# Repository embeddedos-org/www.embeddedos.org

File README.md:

# www.embeddedos.org

The public website of the Embedded Operating Systems Research Foundation.

Community resources: [Wiki](https://github.com/embeddedos-org/www.embeddedos.org/wiki) · [Discussions](https://github.com/orgs/embeddedos-org/discussions) · [Issues](https://github.com/embeddedos-org/www.embeddedos.org/issues) · [Projects](https://github.com/orgs/embeddedos-org/projects) · [AGENTS.md](https://github.com/embeddedos-org/www.embeddedos.org/blob/master/AGENTS.md)

A React single-page application that is **prerendered to static HTML at build
time** — every route ships as a real document with its own `<title>`, meta
description and canonical URL, readable without JavaScript.

**Production has no server process.** The site deploys to cPanel as the static
contents of `dist/public`, served by Apache. There is no `/api/trpc` in
production, and anything that assumes one is broken there even when it works
locally — that is how the careers form silently lost every application it
received, and why eBot and site search now answer entirely in the browser from
`shared/ebot-knowledge.ts` and `shared/site-index.ts`.

The Express + tRPC server in `server/` runs the **development** server and
backs the test suite. Treat any new tRPC procedure as dev-and-test-only unless
the hosting model changes.

---

## Requirements

| Tool    | Version used here | Notes                                                    |
| ------- | ----------------- | -------------------------------------------------------- |
| Node.js | 22                | Matches `.nvmrc`, `engines.node` and the version CI runs |
| pnpm    | 10.4.1            | Pinned by `packageManager` in `package.json`             |

`.nvmrc` pins the major version, so with nvm installed:

```bash
nvm use
```

On a machine where Node is installed in a local toolchain directory rather
than through a version manager, put it on `PATH` in every new shell instead:

```bash
export PATH="$HOME/.local/node/bin:$PATH"
```

Every command below assumes one of those has been done. If
`pnpm: command not found` is the first thing you see, this is why. Do not run
the `pnpm` shim that ships with corepack unless it has already downloaded
pnpm — it fetches on first use and will hang on a slow connection.

---

## Quick start

```bash
export PATH="$HOME/.local/node/bin:$PATH"
pnpm install
pnpm dev          # http://localhost:3000 (falls back to the next free port)
```

To run what actually ships — prerendered HTML, real 404s, the storage proxy —
build first and serve the production bundle:

```bash
pnpm build
pnpm start
```

`pnpm build` runs four steps in order, and all four matter:

1. `optimize:images` — re-encodes images in `client/public` (WebP variants)
2. `build:client` — vite builds the SPA into `dist/public`
3. `prerender` — headless Chromium renders all 133 routes to `<route>/index.html`,
   then `sitemap:dist` writes the sitemap for that exact build
4. `build:server` — esbuild bundles the API server to `dist/index.js`

Running `pnpm build:client` alone produces a build with **no prerendered
pages**. Never deploy that; see [Deployment](#deployment).

---

## Layout

```
client/          React SPA
  src/pages/     One component per route (134 <Route> declarations in App.tsx,
                 133 of them static and therefore prerendered)
  src/components/  Shared UI; components/ui/ is shadcn/Radix primitives
  public/        Copied verbatim into dist/public — including .htaccess and .cpanel.yml
server/          Express + tRPC API
  _core/         Server bootstrap, auth, storage proxy, vite middleware
  routers.ts     tRPC route definitions
shared/          Types and data used by both sides
docs/wiki/       Reviewable, byte-identical mirrors of the repository wiki
scripts/         Build and maintenance tooling (prerender, audits, deploy)
e2e/             Playwright suites
tests/           Vitest suites (unit, integration, security, performance)
drizzle/         Database schema and migrations
dist/            Build output — gitignored, and the source of the deploy branch
```

Governance documents (`CLAUDE.md`, `VERIFY.md`, `TESTING.md`, `SECURITY-STANDARDS.md`,
`AGENTS.md`, …) define how work on this repository is carried out and verified.
`CLAUDE.md` is the entry point and routes to the rest.

---

## Commands

### Build and run

| Command                             | Does                                                    |
| ----------------------------------- | ------------------------------------------------------- |
| `pnpm dev`                          | Development server with HMR                             |
| `pnpm build`                        | Full production build: client → prerender → server      |
| `pnpm build:client`                 | Client only — **no prerendering**, not deployable alone |
| `pnpm prerender`                    | Re-run prerendering against an existing `dist/public`   |
| `pnpm start`                        | Serve the production build                              |
| `pnpm check`                        | TypeScript, no emit                                     |
| `pnpm lint` / `pnpm lint:fix`       | ESLint                                                  |
| `pnpm format` / `pnpm format:check` | Prettier                                                |

### Tests

| Command                 | Covers                                                       |
| ----------------------- | ------------------------------------------------------------ |
| `pnpm test`             | All vitest suites (unit, integration, security, performance) |
| `pnpm test:unit`        | `tests/unit`                                                 |
| `pnpm test:integration` | `tests/integration`                                          |
| `pnpm test:security`    | `tests/security`                                             |
| `pnpm test:perf`        | `tests/performance` — payload budgets                        |
| `pnpm test:e2e`         | Every Playwright suite                                       |
| `pnpm test:smoke`       | `e2e/smoke.spec.ts`                                          |
| `pnpm test:regression`  | `e2e/regression.spec.ts` — one guard per fixed defect        |
| `pnpm test:a11y`        | `e2e/ui-ux.spec.ts` — axe accessibility checks               |
| `pnpm test:journeys`    | Navigation journeys, link and control sweeps                 |
| `pnpm test:controls`    | Clicks every in-page control on every route                  |
| `pnpm test:links`       | On-demand: clicks every internal link, checks where it lands |
| `pnpm test:functional`  | `e2e/functional.spec.ts`                                     |
| `pnpm test:acceptance`  | Google Ad Grants policy criteria                             |
| `pnpm test:server`      | `server/**` tRPC router tests                                |
| `pnpm test:all`         | check → lint → build → test → audits → e2e                   |

Three suites cover controls, and the differences matter — each catches what the
one before it cannot:

- `test:journeys` reads the **built HTML** and proves each of the ~9,000
  anchors resolves and each of the ~1,100 buttons carries an accessible name.
  It presses nothing.
- `test:controls` **clicks** every one of the ~340 in-page controls across all
  133 routes, plus the header and footer controls on a sample, and fails on any
  uncaught exception or console error. A control can pass the first suite and
  still throw on click.
- `test:links` clicks each of the ~320 unique internal links **from the bottom
  of its page** and asserts two things the others never check: that it lands on
  the route its href names, and that the page opens at the top.

`test:links` is **opt-in and skipped by `pnpm test:e2e`**, which is why it
needs its own command. It performs ~320 real navigations and proved sensitive
to machine load in a way the rest of the suite is not: under parallel workers a
different page each run reported resting a few hundred pixels down, and none of
it reproduced — twelve controlled navigations from the worst offender measured
y=0 every time, and none of the implicated pages contains scrolling, focus or
iframe code that could explain it. A check that fails one test in eighty for
reasons outside the code teaches people to ignore red, so it is a diagnostic
rather than a gate. The defects it originally found are guarded deterministically
by the scroll tests in `regression.spec.ts`, which fail when the fix is removed.

Run it before a release, and read a failure as "look at this", not "this is broken".

The Playwright suites run against the **production build**, and
`playwright.config.ts` starts `dist/index.js` for them. Run `pnpm build` first,
or the suite tests a stale build. Several tests read `dist/public` directly.

### Audits

| Command                | Does                                          |
| ---------------------- | --------------------------------------------- |
| `pnpm audit:site`      | Crawls the built site for structural problems |
| `pnpm audit:mobile`    | Mobile-viewport audit                         |
| `pnpm optimize:images` | Re-encodes images in `client/public`          |
| `pnpm sync:stack`      | Refreshes generated stack data                |

---

## Deployment

The site is hosted on **cPanel**, served by Apache as static files, and updated
through cPanel's Git Version Control feature.

### How the `deploy` branch works

`deploy` is an **orphan branch** — it shares no history with `master` — whose
root is exactly the contents of `dist/public`. It holds build output, not
source. Its commits read `deploy: rebuild from master <sha>`, which is the only
link back to the source they were built from.

```
master   ──●──●──●──●   source
                  │
                  │  pnpm build  →  dist/public
                  ▼
deploy   ──●──●──●       built site, root = dist/public
                  │
                  ▼  cPanel: Update from Remote → Deploy HEAD Commit
             public_html/
```

Two files make this work, and both live in `client/public/` so that **vite
copies them into every build**:

- **`.htaccess`** — `Options -Indexes` and `ErrorDocument 404 /404.html`.
  Deliberately **no SPA rewrite**: the prerenderer writes every route to
  `<route>/index.html`, so Apache's ordinary file resolution already serves
  them. A blanket rewrite to `/index.html` answers unknown URLs with HTTP 200
  and the homepage — a soft 404 that search engines index as a real page.
- **`.cpanel.yml`** — the tasks cPanel runs on deploy. It copies `*` plus
  `.htaccess` by name, because the `*` glob skips dotfiles. There is no delete
  step: overwriting is safe, emptying a directory is not. Before copying the
  build, it appends `session.upload_progress.enabled = 0` to
  `public_html/.user.ini` unless the file already ends up at 0, a stopgap for
  #128 that `.htaccess` repeats for module handlers; `.htaccess` also denies
  web access to `.user.ini`. It appends rather than copies so the host's own
  PHP settings in that file survive. The fix for #128 is still upgrading the
  host's PHP in cPanel.
  Each deploy replaces `public_html/.htaccess`. Under some PHP handlers
  cPanel's MultiPHP Manager and INI Editor write their settings into that
  file, so check the live file before changing PHP in cPanel, or the next
  deploy will drop those settings.

They live in `client/public/` rather than being committed to `deploy` directly
because that was tried and it failed — a file added to the deploy branch by hand
is deleted by the next rebuild, which is exactly how `.htaccess` once went
missing from production. `tests/integration/deploy-config.test.ts` asserts both
files reach `dist/public` and that the rules inside them are still correct.

### Deploying

The one-command path — build, publish to the `deploy` branch, push:

```bash
./deploy.sh                     # full pipeline, pushes to origin
./deploy.sh --no-push           # stop after committing to deploy, for review
```

Or the manual steps, which `./deploy.sh` chains for you:

```bash
export PATH="$HOME/.local/node/bin:$PATH"

# 1. Everything must be green and committed first.
pnpm test:all
git status --porcelain          # must be empty

# 2. Build, then publish the build to the deploy branch.
pnpm build
pnpm deploy:branch              # commits to deploy, does NOT push
git log deploy -1 --stat        # review what is about to ship
pnpm deploy:branch --push       # or: git push origin deploy
```

`scripts/deploy-branch.mjs` does the mechanical part through a throwaway git
worktree, so the checkout you are working in is never switched to `deploy`
mid-run. It refuses to proceed if:

- there is no build in `dist/public`;
- fewer than 50 routes were prerendered (i.e. `build:client` was run without
  `prerender`);
- `.htaccess` or `.cpanel.yml` is missing from the build;
- the working tree is dirty, which would make the recorded source sha a lie.

It replaces the branch contents wholesale, so superseded content-hashed bundles
are pruned from the branch rather than accumulating.

**Pushing is not deploying.** cPanel does not act on a push. Finish in the
cPanel UI:

> Git Version Control → Manage (for this repository) → **Update from Remote**,
> then **Deploy HEAD Commit**.

`DEPLOYPATH` in `.cpanel.yml` is `$HOME/public_html`. Change it if this domain's
document root is elsewhere — an addon domain or subdomain has its own directory.

### Rolling back

The deploy branch is an ordinary branch, so a rollback is a revert plus another
deploy:

```bash
git checkout deploy
git revert --no-edit HEAD        # or: git reset --hard <known-good-sha>
git push origin deploy           # --force-with-lease if you reset
# then in cPanel: Update from Remote → Deploy HEAD Commit
```

Because `.cpanel.yml` has no delete step, files removed in a later build are
**not** removed from the document root by deploying an earlier commit. Files
that must genuinely disappear from production have to be deleted on the server.

---

## Environment variables

There is no `.env.example` in the repository. The following are the variables
referenced in the source; the site builds and serves its static content without
them, but the API features that use them are inert when unset.

| Variable                                           | Used for                                                                                                                                                                                            |
| -------------------------------------------------- | --------------------------------------------------------------------------------------------------------------------------------------------------------------------------------------------------- |
| `PORT`                                             | Server port (default 3000; the server scans forward for a free one)                                                                                                                                 |
| `NODE_ENV`                                         | `development` / `production`                                                                                                                                                                        |
| `DATABASE_URL`                                     | MySQL connection for drizzle                                                                                                                                                                        |
| `JWT_SECRET`                                       | Cookie/session signing                                                                                                                                                                              |
| `OAUTH_SERVER_URL`, `OWNER_OPEN_ID`, `VITE_APP_ID` | OAuth integration                                                                                                                                                                                   |
| `STRIPE_SECRET_KEY`                                | Card payments on /donate (Stripe secret key — set on the host only, never in git; see `docs/STRIPE-SECRET-KEY.md`)                                                                                  |
| `SMTP_HOST`, `SMTP_PORT`, `SMTP_USER`, `SMTP_PASS` | Outbound email                                                                                                                                                                                      |
| `BUILT_IN_FORGE_API_URL`, `BUILT_IN_FORGE_API_KEY` | Manus Forge API — backs the dev/test-only owner-notification and image-storage-proxy code paths in `server/_core/`. Not used in production; the live careers form posts to `/api/apply.php` instead |
| `SITE_ORIGIN`                                      | Canonical origin used by the prerenderer (default `https://www.embeddedos.org`)                                                                                                                     |
| `PRERENDER_PORT`, `PRERENDER_CONCURRENCY`          | Prerender tuning                                                                                                                                                                                    |
| `E2E_PORT`                                         | Port Playwright's server uses (default 42200)                                                                                                                                                       |

Database schema changes go through `pnpm db:push` (drizzle-kit generate +
migrate).

---

## Booking

`/book` is the booking page, linked as "Book a call" in the header. `/contact`
and `/eos-boards` each carry a compact card that links to it. The page is
`client/src/pages/Book.tsx`: it lists the topics as guidance and embeds the
Foundation's Google Calendar appointment schedule
(`client/src/components/BookingCalendar.tsx`), where the visitor picks a time
and fills in Google's booking form. Topics, durations, the "what to expect"
list and the FAQ are in `client/src/data/booking.ts`.

- **The calendar is two constants** in `client/src/data/foundation.ts`:
  - `GOOGLE_APPOINTMENTS_EMBED_URL`, the iframe `src` from the schedule's
    embed code, now
    `https://calendar.google.com/calendar/appointments/AcZssZ3QwWoaBjMsLfr11qrGiRxBA4URKeZ8Zu-5bv0=?gv=true`;
  - `GOOGLE_BOOKING_PAGE_URL`, the schedule's booking page link, now
    `https://calendar.app.google/PPzWao4AzvXtZeva6`. It sits under the
    calendar as "Open the booking page" and opens in a new tab.
- **To change the calendar,** open the appointment schedule in Google
  Calendar and use its share options: copy the booking page link into
  `GOOGLE_BOOKING_PAGE_URL`, and from the website embed code copy only the
  `src` of the `<iframe>` into `GOOGLE_APPOINTMENTS_EMBED_URL`. Do not paste
  Google's "Book an appointment" button code: it loads
  `scheduling-button-script.js` and a stylesheet from Google, which the CSP
  does not allow and the site does not use. `client/src/lib/booking.ts`
  accepts only these forms:
  - embed: `https://calendar.google.com/calendar/appointments/<id>?gv=true`
    (optionally `appointments/schedules/<id>`);
  - booking page: `https://calendar.app.google/<id>`, or the
    `https://calendar.google.com/calendar/appointments/...` address without
    the query.

  Then update `tests/unit/booking-url-set.test.tsx`, which pins both values.
  An embed URL that does not pass the check shows the email fallback instead
  of a calendar, with the `_BY_EMAIL` versions of the steps, the "what to
  expect" list, the time-zone note and the FAQ, which promise only an email
  reply; a booking link that does not pass is left out.

- **Set in Google Calendar, not here:** the slot length, the video link and the
  booking form. The cards and copy say 30 minutes (`BOOKING_MINUTES`) and a
  video link in the confirmation email, so the schedule must use 30-minute
  slots with Google Meet (or another video link). The page asks visitors to
  mention their topic in the booking form, which by default asks only for a
  first name, a last name and an email address, so give the form an item such
  as "What would you like to talk about?". Nothing in this repository can check these settings;
  confirm them on the schedule.
- **The topic can no longer be passed in:** Google's embed takes no prefill,
  so the topic cards are guidance, not inputs, and the three steps are a guide
  rather than a progress bar.
- **Loading:** the iframe is mounted when the card comes within 300 px of the
  viewport, never while the site is prerendered, and carries
  `loading="lazy"`. A skeleton shows until the frame's load event. If that has
  not fired after 15 s (`FRAME_TIMEOUT_MS`), the card offers the booking page
  and the email option over it, and the calendar takes over again if it loads
  after all. The browser fires load even for an error page in the frame, so
  the link under the calendar is always shown.
- **CSP:** `client/public/.htaccess` allows `https://calendar.google.com` in
  `frame-src` and adds no Google script or style host for the calendar.
- **Notifications:** the embedded calendar tells this site nothing about a
  booking, so the site sends no notice of its own and stores nothing. Google
  adds each booking to the schedule owner's calendar ("When someone books an
  appointment, it's added to your calendar", Google Calendar Help). Any email
  about it, to the booker or to the team, is decided by the appointment
  schedule's own settings in Google Calendar, which also set up "confirmation
  emails and reminders" (Google Calendar Help, "Create an appointment
  schedule"). Check there that the booker gets a confirmation email, which the
  FAQ promises along with its cancel link, and that the team learns of each
  booking, by email or by watching the calendar.
- **`client/public/api/booking.php` is retired.** It used to mail the team a
  notice posted by the previous calendar. It now answers every request with
  HTTP 410 and does nothing else (`tests/php/booking-retired.test.php` and
  `tests/unit/booking.test.tsx` pin that). It stays because the cPanel deploy
  (`client/public/.cpanel.yml`) copies files and never deletes: removed from
  the repository, the old endpoint would stay live on the server. After this
  version is deployed, delete `public_html/api/booking.php` on the server, then
  delete the file here. That deletion turns CI's `deploy-drift` job red until
  the deploy branch is next rebuilt with `scripts/deploy-branch.mjs`, because
  `scripts/check-deploy-drift.mjs` fails on files the deploy branch has and the
  build does not; rebuild it soon after.

## Notes for contributors

- **Do not render `<Navbar />` or `<Footer />` inside a page.** `App.tsx`
  renders both around `<main>` for the whole application. A page that adds its
  own produces a second `position: fixed; z-50` header which, being later in the
  DOM, silently swallows every click aimed at the real one. This shipped once
  and disabled the navigation on all 13 product pages and `/patents`.
  `e2e/links-and-controls.spec.ts` now fails the build if it recurs.
- **Every route needs a prerendered page.** Routes are discovered from the
  literal `<Route path="...">` strings in `App.tsx`; anything dynamic is skipped
  and will 404 on the static host. `tests/integration/deploy-config.test.ts`
  checks each discovered route has a file.
- **Never hand-write a stack figure.** Board counts, platform counts, repo
  counts and architecture counts come from `shared/stack-data.ts` via
  `client/src/data/stack.ts` — import the constant, do not type the number.
  Hand-written figures have drifted twice: "52+" survived on seventeen pages,
  and after that purge "63+" survived on nineteen more, describing EoSim's
  150 simulated _platforms_ as 63 _boards_ and colliding with the kernel's 83
  board definitions. `tests/integration/stack-claims.test.ts` scans every built
  page and fails if a retired figure reappears. `/news` is exempt: its posts
  are dated announcements, and rewriting one revises the record rather than
  correcting a claim.
- **`<head>` is stamped twice, by two implementations that must agree.**
  `scripts/prerender.mjs` writes it at build time; `client/src/lib/page-meta.ts`
  rewrites it after a client-side navigation, because wouter swaps the page
  without touching `<head>` and the canonical URL would otherwise keep naming
  the first page visited. The build script cannot be imported into the bundle
  (it pulls in playwright and express), so the logic is deliberately duplicated
  and `tests/unit/page-meta.test.ts` asserts the two agree.
- **A route change must reset the scroll position.** wouter swaps the page
  component and leaves the viewport alone, so a link followed from the footer
  opened the next page already scrolled down — the browser clamps the old
  offset to the new document's height. `ScrollToTop` in `App.tsx` handles it,
  and three cases are easy to get wrong: the jump must be `behavior: "instant"`
  because `index.css` sets `scroll-behavior: smooth` for in-page anchors; a
  link to the route **already open** produces no location change at all, so it
  needs a capture-phase click listener (wouter's `Link` calls `preventDefault`,
  which makes a bubble-phase listener useless); and a `#hash` target must win
  over the jump to the top.
- **Never call `scrollIntoView` to follow a list.** It scrolls _every_ ancestor
  scroll container, including the document. `/demo` auto-scrolled its simulator
  log that way and the effect ran on mount, so opening the page dropped the
  visitor below the heading. Set the container's own `scrollTop` instead.
- **A modal must take focus.** The donate dialog shipped with
  `aria-modal="true"` and focus left on `<body>`, so one Tab reached the
  navigation behind the overlay. If you add an overlay, move focus into it,
  trap Tab, restore focus on close, and close on Escape.
- **`flex-1` without `min-w-0` overflows on a phone.** A flex item defaults to
  `min-width: auto`, so a code block or long string inside sizes the item to its
  content and pushes the document wider than the viewport. Six pages shipped
  this way. Wide tables need their own `overflow-x-auto` wrapper for the same
  reason.
- **framer-motion cannot tween an SVG `d` attribute.** It emits
  `d="undefined"` mid-tween. Animate a transform instead. An entry animation
  that starts at `x: ±20` also overflows a 375px viewport until it settles —
  clip the section.
- Payload budgets are enforced in `tests/performance/budgets.test.ts`; adding a
  large eager import will fail the suite rather than quietly regress the site.
- **A new board on `/eos-boards` is one manifest entry plus its media, its
  two KiCad files and its licence.** Add the board to `EOS_BOARDS` in
  `client/src/data/eos-boards.ts`, copying its facts from the board's
  `README.md` and its check counts from `build-report.json` and `drc.json` in
  eCAD-Hardware-Products. Put its media in `client/public/media/`:
  `board-<slug>-iso.jpg`, `-top.jpg` and `-bottom.jpg` from the board's
  renders, `board-<slug>-thumb.jpg` (the iso render at 480 px, for the index),
  `board-<slug>-turntable.mp4` (H.264, no audio) and
  `board-<slug>-turntable-poster.jpg` (the video's first frame). Copy, unchanged
  and from the commit in `checks.commit`, its native files
  `boards/eos/<slug>/hardware/<slug>.kicad_sch` and `<slug>.kicad_pcb` to
  `client/public/cad/<slug>/`, and its `boards/eos/<slug>/LICENSE.txt` to
  `client/public/board-licences/<slug>.txt` (`git show <commit>:<path>` in
  eCAD-Hardware-Products gives the exact bytes).
  Set `source` to `BOARD_SOURCES.merged`: the page lists only boards merged on
  eCAD-Hardware-Products master. Set `checks.commit` to the commit its counts
  come from. Then run `pnpm optimize:images` for the WebP siblings and the manifest.
  `tests/unit/eos-boards.test.tsx` fails if a media, KiCad or licence file is
  missing, a declared pixel size is wrong, or a KiCad file or licence does not
  carry the owner's name and terms.

---

## Licence

MIT, except the EmbeddedOS development-board renders and turntable videos in
`client/public/media/board-*`, the boards' native KiCad files in
`client/public/cad/`, and the board licences in `client/public/board-licences/`
(each board's `LICENSE.txt`, unchanged). Those are Copyright (c) 2026
Kartikeydheer Srivastava, all rights reserved, and are published here for
viewing under each board's `LICENSE.txt` in eCAD-Hardware-Products; see
`/eos-boards`. Third-party material in a board keeps its own licence, as that
board's licence lists.

See [SECURITY.md](./SECURITY.md) for the vulnerability disclosure policy.

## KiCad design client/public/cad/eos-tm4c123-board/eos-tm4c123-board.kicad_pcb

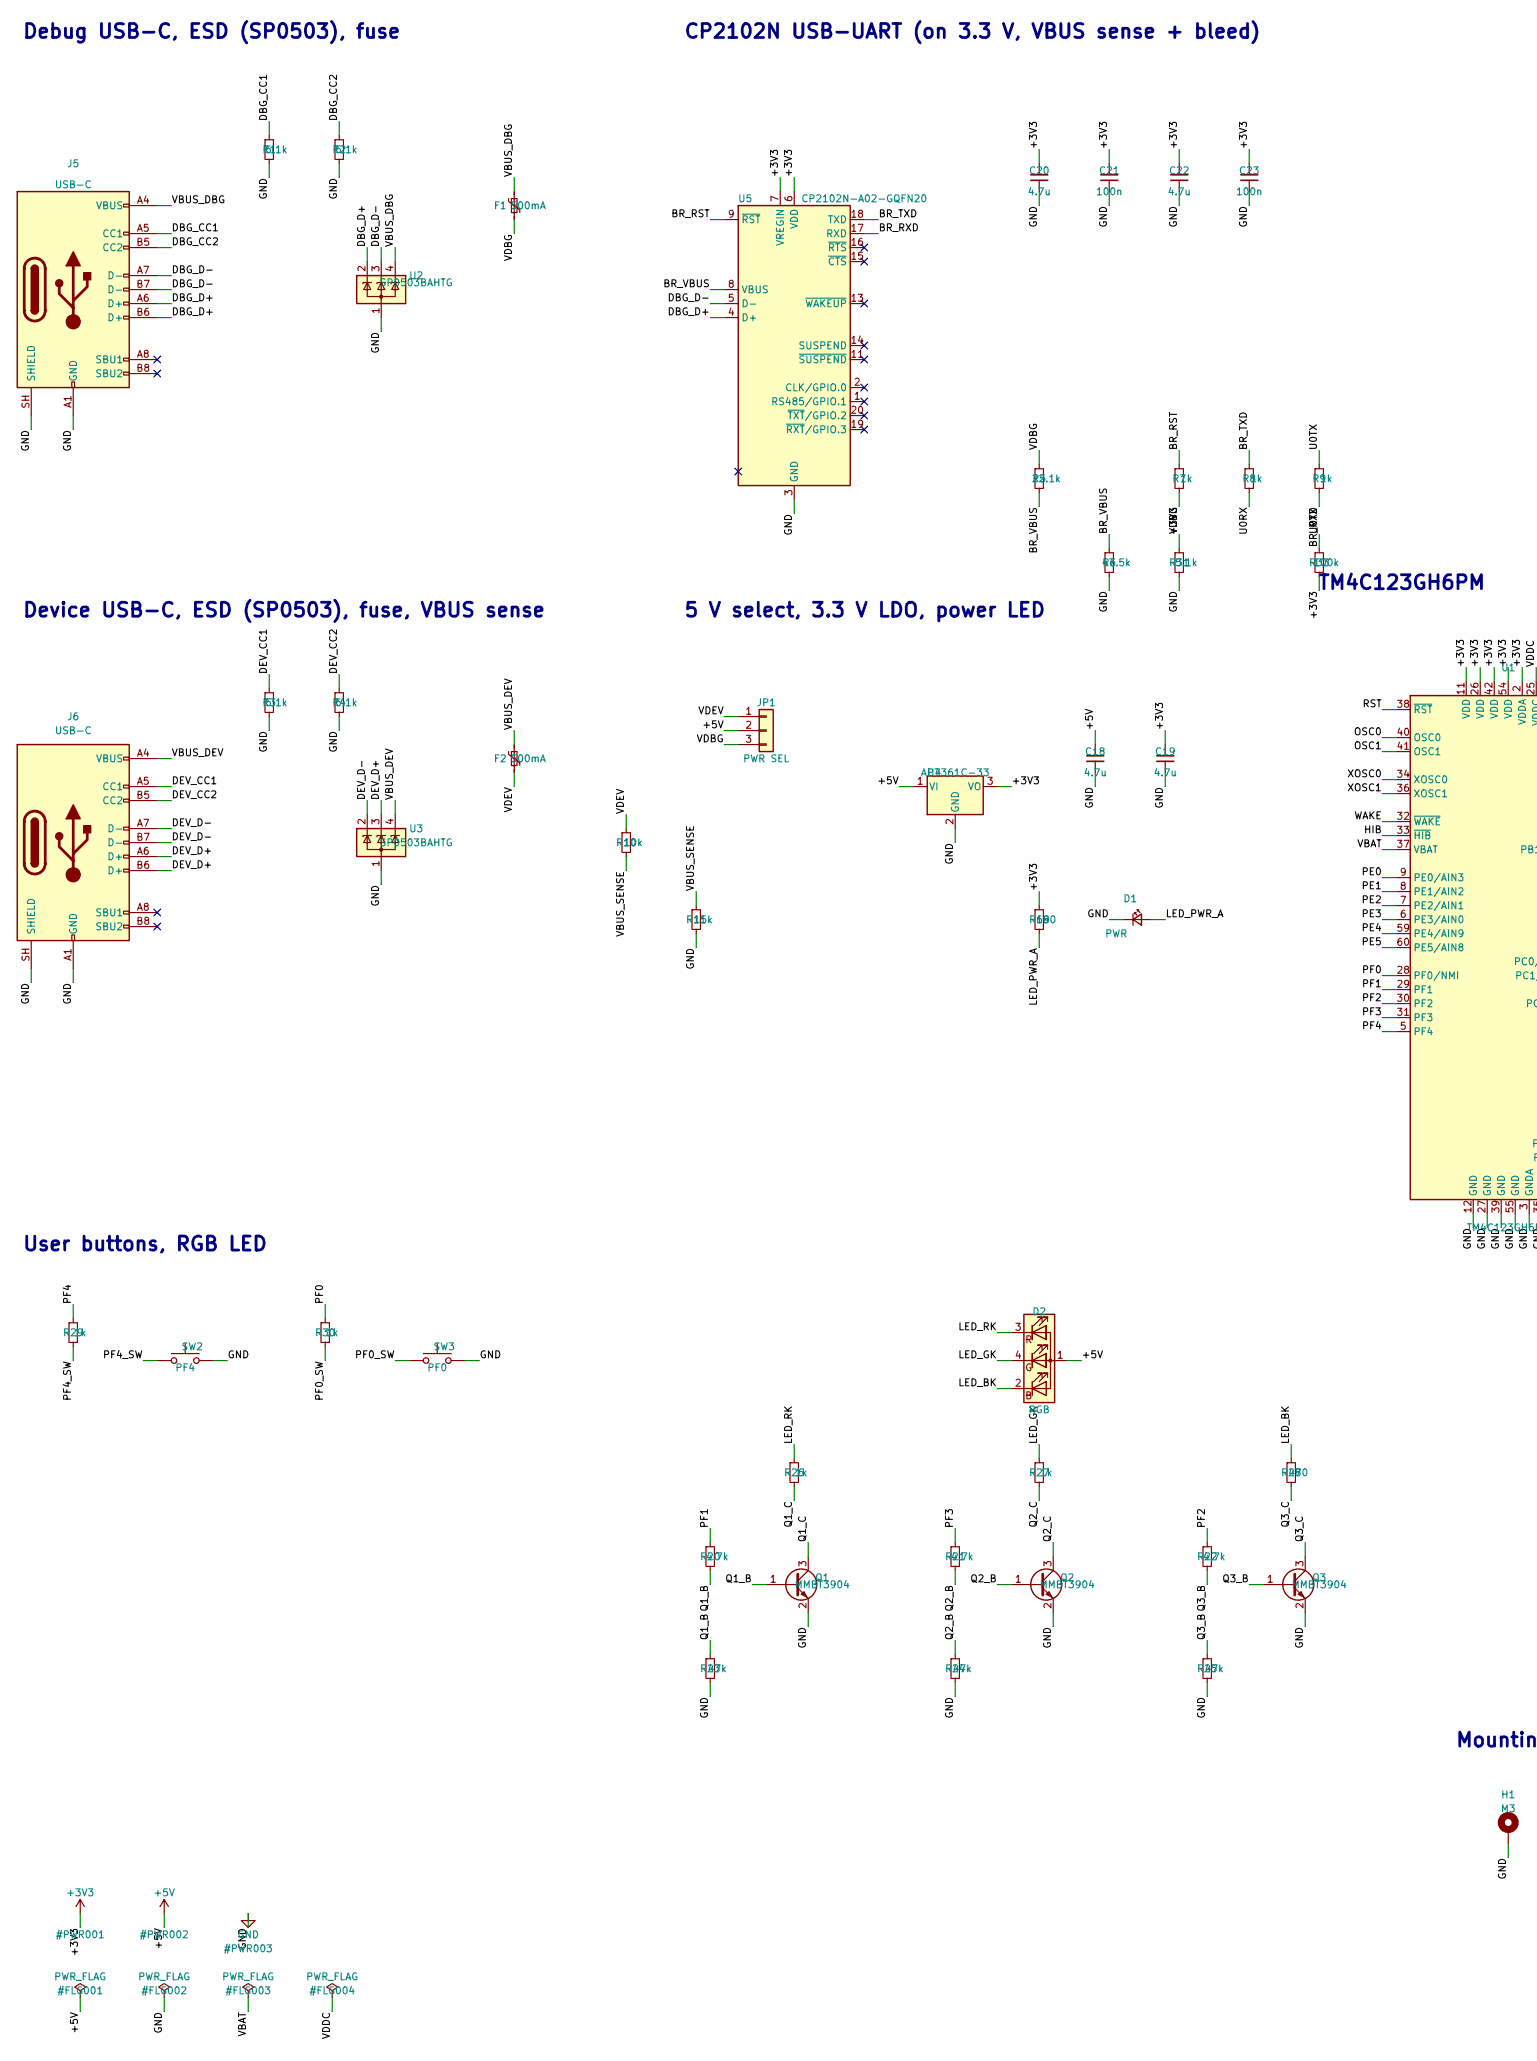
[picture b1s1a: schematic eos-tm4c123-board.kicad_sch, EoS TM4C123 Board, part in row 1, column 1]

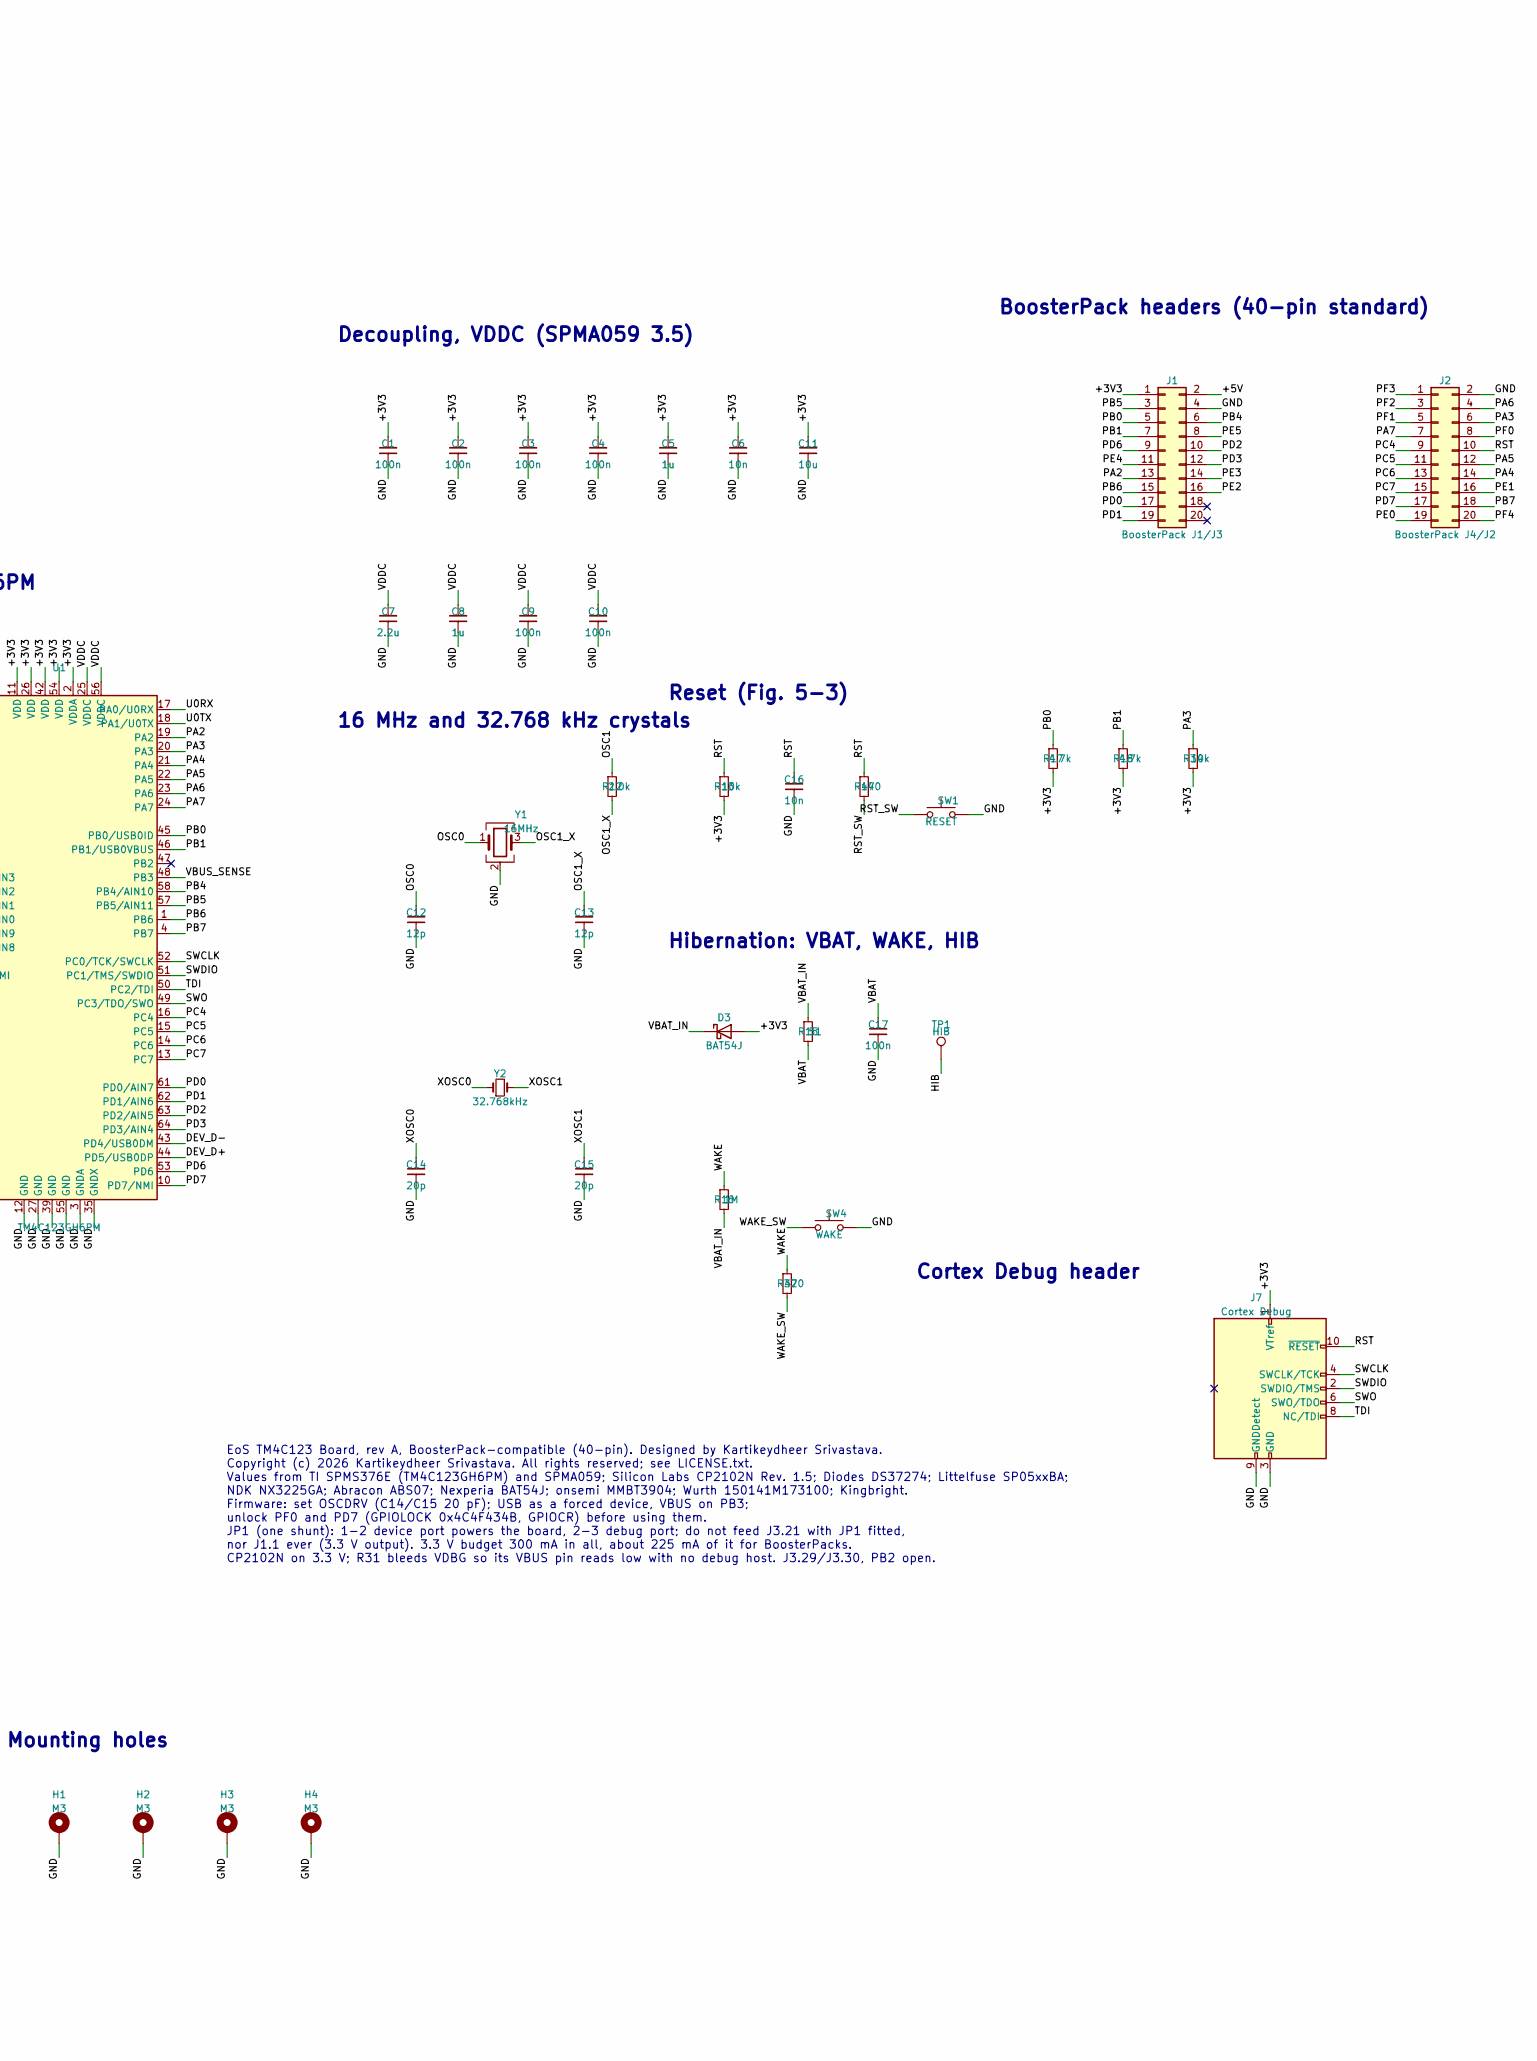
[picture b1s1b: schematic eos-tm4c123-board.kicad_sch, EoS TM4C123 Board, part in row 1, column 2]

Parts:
C1, C2, C3, C4, C9, C10, C17, C21, C23: 100n; C_0402_1005Metric; MPN GRM155R71C104KA88D
C5, C8: 1u; C_0603_1608Metric; MPN GRM188R71C105KA12D
C6, C16: 10n; C_0402_1005Metric; MPN GRM155R71H103KA88D
C7: 2.2u; C_0603_1608Metric; MPN GRM188R71A225KE15D
C11: 10u; C_0805_2012Metric; MPN GRM21BR61A106KE19L
C12, C13: 12p; C_0402_1005Metric; MPN GRM1555C1H120JA01D
C14, C15: 20p; C_0402_1005Metric; MPN GRM1555C1H200JA01D
C18, C19: 4.7u; C_0805_2012Metric; MPN GRM21BR61A475KA73L
C20, C22: 4.7u; C_0603_1608Metric; MPN GRM188R61A475KE15D
D1: PWR; LED_0603_1608Metric; MPN APTD1608LCGCK
D2: RGB; LED_RGB_Wuerth-PLCC4_3.2x2.8mm_150141M173100; MPN 150141M173100
D3: BAT54J; D_SOD-323F; MPN BAT54J
F1, F2: 500mA; Fuse_1206_3216Metric; MPN 1206L050YR
H1, H2, H3, H4: M3; MountingHole_3.2mm_M3_Pad_Via
J1: BoosterPack J1/J3; PinHeader_2x10_P2.54mm_Vertical; MPN SSW-110-23-F-D
J2: BoosterPack J4/J2; PinHeader_2x10_P2.54mm_Vertical; MPN SSW-110-23-F-D
J5, J6: USB-C; USB_C_Receptacle_HRO_TYPE-C-31-M-12; MPN TYPE-C-31-M-12
J7: Cortex Debug; PinHeader_2x05_P1.27mm_Vertical_SMD; MPN FTSH-105-01-L-DV-K
JP1: PWR SEL; PinHeader_1x03_P2.54mm_Vertical
Q1, Q2, Q3: MMBT3904; SOT-23; MPN MMBT3904LT1G
R1, R2, R3, R4, R31: 5.1k; R_0402_1005Metric
R5: 22.1k; R_0402_1005Metric
R6: 47.5k; R_0402_1005Metric
R7, R8, R9, R26, R27, R29, R30: 1k; R_0402_1005Metric
R10, R13, R34: 10k; R_0402_1005Metric
R11: 15k; R_0402_1005Metric
R12: 2.0k; R_0402_1005Metric
R14, R28, R32: 470; R_0402_1005Metric
R15: 51; R_0402_1005Metric
R16: 1M; R_0402_1005Metric
R17, R18, R20, R21, R22: 4.7k; R_0402_1005Metric
R19: 680; R_0402_1005Metric
R23, R24, R25: 47k; R_0402_1005Metric
R33: 100k; R_0402_1005Metric
SW1: RESET; SW_Push_1P1T_NO_CK_KMR2; MPN KMR221G LFS
SW2: PF4; SW_Push_1P1T_NO_CK_KMR2; MPN KMR221G LFS
SW3: PF0; SW_Push_1P1T_NO_CK_KMR2; MPN KMR221G LFS
SW4: WAKE; SW_Push_1P1T_NO_CK_KMR2; MPN KMR221G LFS
TP1: HIB; TestPoint_Pad_D1.0mm
U1: TM4C123GH6PM; LQFP-64_10x10mm_P0.5mm; MPN TM4C123GH6PMI
U2, U3: SP0503BAHTG; SOT-143; MPN SP0503BAHTG
U4: AP7361C-33; SOT-223-3_TabPin2; MPN AP7361C-33E-13
U5: CP2102N-A02-GQFN20; SiliconLabs_QFN-20-1EP_3x3mm_P0.5mm_EP1.8x1.8mm; MPN CP2102N-A02-GQFN20R
Y1: 16MHz; Crystal_SMD_3225-4Pin_3.2x2.5mm; MPN NX3225GA-16.000M-STD-CRG-2
Y2: 32.768kHz; Crystal_SMD_3215-2Pin_3.2x1.5mm; MPN ABS07-32.768KHZ-T

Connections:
+3V3: C1.1, C2.1, C3.1, C4.1, C5.1, C6.1, C11.1, C19.1, C20.1, C21.1, C22.1, C23.1, D3.2 (A), J1.1, J7.1 (VTref), R7.2, R13.2, R17.2, R18.2, R19.1, R33.2, R34.2, U1.2 (VDDA), U1.11 (VDD), U1.26 (VDD), U1.42 (VDD), U1.54 (VDD), U4.3 (VO), U5.6 (VDD), U5.7 (VREGIN)
+5V: C18.1, D2.1 (A), J1.2, JP1.2, U4.1 (VI)
/BR_RST: R7.1, U5.9 (~RST)
/BR_RXD: R9.2, U5.17 (RXD)
/BR_TXD: R8.1, U5.18 (TXD)
/BR_VBUS: R5.2, R6.1, U5.8 (VBUS)
/DBG_CC1: J5.A5 (CC1), R1.1
/DBG_CC2: J5.B5 (CC2), R2.1
/DBG_D+: J5.A6 (D+), J5.B6 (D+), U2.2 (K), U5.4 (D+)
/DBG_D-: J5.A7 (D-), J5.B7 (D-), U2.3 (K), U5.5 (D-)
/DEV_CC1: J6.A5 (CC1), R3.1
/DEV_CC2: J6.B5 (CC2), R4.1
/DEV_D+: J6.A6 (D+), J6.B6 (D+), U1.44 (PD5/USB0DP), U3.3 (K)
/DEV_D-: J6.A7 (D-), J6.B7 (D-), U1.43 (PD4/USB0DM), U3.2 (K)
/HIB: TP1.1, U1.33 (~HIB)
/LED_BK: D2.2 (BK), R28.1
/LED_GK: D2.4 (GK), R27.1
/LED_PWR_A: D1.2 (A), R19.2
/LED_RK: D2.3 (RK), R26.1
/OSC0: C12.1, U1.40 (OSC0), Y1.1
/OSC1: R12.1, U1.41 (OSC1)
/OSC1_X: C13.1, R12.2, Y1.3
/PA2: J1.13, U1.19 (PA2)
/PA3: J2.6, R34.1, U1.20 (PA3)
/PA4: J2.14, U1.21 (PA4)
/PA5: J2.12, U1.22 (PA5)
/PA6: J2.4, U1.23 (PA6)
/PA7: J2.7, U1.24 (PA7)
/PB0: J1.5, R17.1, U1.45 (PB0/USB0ID)
/PB1: J1.7, R18.1, U1.46 (PB1/USB0VBUS)
/PB4: J1.6, U1.58 (PB4/AIN10)
/PB5: J1.3, U1.57 (PB5/AIN11)
/PB6: J1.15, U1.1 (PB6)
/PB7: J2.18, U1.4 (PB7)
/PC4: J2.9, U1.16 (PC4)
/PC5: J2.11, U1.15 (PC5)
/PC6: J2.13, U1.14 (PC6)
/PC7: J2.15, U1.13 (PC7)
/PD0: J1.17, U1.61 (PD0/AIN7)
/PD1: J1.19, U1.62 (PD1/AIN6)
/PD2: J1.10, U1.63 (PD2/AIN5)
/PD3: J1.12, U1.64 (PD3/AIN4)
/PD6: J1.9, U1.53 (PD6)
/PD7: J2.17, U1.10 (PD7/NMI)
/PE0: J2.19, U1.9 (PE0/AIN3)
/PE1: J2.16, U1.8 (PE1/AIN2)
/PE2: J1.16, U1.7 (PE2/AIN1)
/PE3: J1.14, U1.6 (PE3/AIN0)
/PE4: J1.11, U1.59 (PE4/AIN9)
/PE5: J1.8, U1.60 (PE5/AIN8)
/PF0: J2.8, R30.1, U1.28 (PF0/NMI)
/PF0_SW: R30.2, SW3.1
/PF1: J2.5, R20.1, U1.29 (PF1)
/PF2: J2.3, R22.1, U1.30 (PF2)
/PF3: J2.1, R21.1, U1.31 (PF3)
/PF4: J2.20, R29.1, U1.5 (PF4)
/PF4_SW: R29.2, SW2.1
/Q1_B: Q1.1 (B), R20.2, R23.1
/Q1_C: Q1.3 (C), R26.2
/Q2_B: Q2.1 (B), R21.2, R24.1
/Q2_C: Q2.3 (C), R27.2
/Q3_B: Q3.1 (B), R22.2, R25.1
/Q3_C: Q3.3 (C), R28.2
/RST: C16.1, J2.10, J7.10 (~RESET), R13.1, R14.1, U1.38 (~RST)
/RST_SW: R14.2, SW1.1
/SWCLK: J7.4 (SWCLK/TCK), U1.52 (PC0/TCK/SWCLK)
/SWDIO: J7.2 (SWDIO/TMS), U1.51 (PC1/TMS/SWDIO)
/SWO: J7.6 (SWO/TDO), U1.49 (PC3/TDO/SWO)
/TDI: J7.8 (NC/TDI), U1.50 (PC2/TDI)
/U0RX: R8.2, U1.17 (PA0/U0RX)
/U0TX: R9.1, R33.1, U1.18 (PA1/U0TX)
/VBAT: C17.1, R15.2, U1.37 (VBAT)
/VBAT_IN: D3.1 (K), R15.1, R16.2
/VBUS_DBG: F1.1, J5.A4 (VBUS), J5.A9 (VBUS), J5.B4 (VBUS), J5.B9 (VBUS), U2.4 (K)
/VBUS_DEV: F2.1, J6.A4 (VBUS), J6.A9 (VBUS), J6.B4 (VBUS), J6.B9 (VBUS), U3.4 (K)
/VBUS_SENSE: R10.2, R11.1, U1.48 (PB3)
/VDBG: F1.2, JP1.3, R5.1, R31.1
/VDDC: C7.1, C8.1, C9.1, C10.1, U1.25 (VDDC), U1.56 (VDDC)
/VDEV: F2.2, JP1.1, R10.1
/WAKE: R16.1, R32.1, U1.32 (~WAKE)
/WAKE_SW: R32.2, SW4.1
/XOSC0: C14.1, U1.34 (XOSC0), Y2.1
/XOSC1: C15.1, U1.36 (XOSC1), Y2.2
GND: C1.2, C2.2, C3.2, C4.2, C5.2, C6.2, C7.2, C8.2, C9.2, C10.2, C11.2, C12.2, C13.2, C14.2, C15.2, C16.2, C17.2, C18.2, C19.2, C20.2, C21.2, C22.2, C23.2, D1.1 (K), H1.1, H2.1, H3.1, H4.1, J1.4, J2.2, J5.A1 (GND), J5.A12 (GND), J5.B1 (GND), J5.B12 (GND), J5.SH (SHIELD), J6.A1 (GND), J6.A12 (GND), J6.B1 (GND), J6.B12 (GND), J6.SH (SHIELD), J7.3 (GND), J7.5 (GND), J7.9 (GNDDetect), Q1.2 (E), Q2.2 (E), Q3.2 (E), R1.2, R2.2, R3.2, R4.2, R6.2, R11.2, R23.2, R24.2, R25.2, R31.2, SW1.2, SW2.2, SW3.2, SW4.2, U1.3 (GNDA), U1.12 (GND), U1.27 (GND), U1.35 (GNDX), U1.39 (GND), U1.55 (GND), U2.1 (A), U3.1 (A), U4.2 (GND), U5.3 (GND), U5.12 (GND), U5.21 (GND), Y1.2 (G), Y1.4 (G)

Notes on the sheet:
Debug USB-C, ESD (SP0503), fuse
CP2102N USB-UART (on 3.3 V, VBUS sense + bleed)
Device USB-C, ESD (SP0503), fuse, VBUS sense
5 V select, 3.3 V LDO, power LED
TM4C123GH6PM
Decoupling, VDDC (SPMA059 3.5)
16 MHz and 32.768 kHz crystals
Reset (Fig. 5-3)
Hibernation: VBAT, WAKE, HIB
BoosterPack headers (40-pin standard)
Cortex Debug header
User buttons, RGB LED
Mounting holes
EoS TM4C123 Board, rev A, BoosterPack-compatible (40-pin). Designed by Kartikeydheer Srivastava. Copyright (c) 2026 Kartikeydheer Srivastava. All rights reserved; see LICENSE.txt. Values from TI SPMS376E (TM4C123GH6PM) and SPMA059; Silicon Labs CP2102N Rev. 1.5; Diodes DS37274; Littelfuse SP05xxBA;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

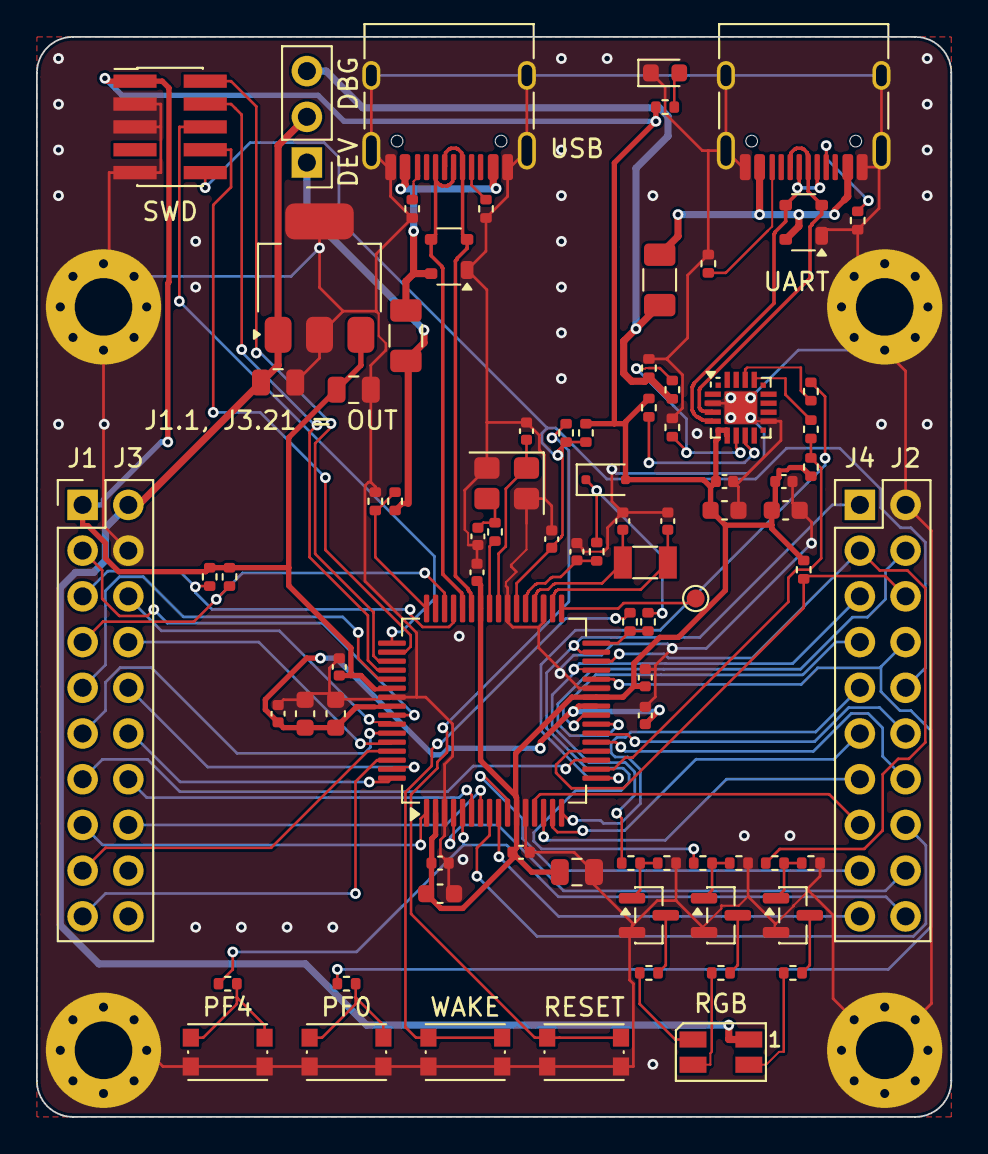
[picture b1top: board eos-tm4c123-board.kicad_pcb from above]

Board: 2 copper layers, 50.8 x 60.0 mm, 87 parts (0 on the bottom side), 84 nets.

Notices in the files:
cad/eos-lpc55s69-board/eos-lpc55s69-board.kicad_sch:
Copyright (c) 2026 Kartikeydheer Srivastava. Licence: All rights reserved
Uno R3 outline (2700 x 2100 mil) and shield header positions: Matthew Beckler, \"Arduino Uno R3\" dimension drawing v1.05, Wayne and Layne, public domain (wayneandlayne.com/files/common/arduino_uno_drawing.svg); facts only, no file copied
